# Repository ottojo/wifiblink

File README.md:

## Wiring
| Shield |  GPIO   | WEMOS |
|--------|:-------:|------:|
| Output | GPIO 14 |    D5 |
| LED 1  | GPIO 12 |    D6 |
| LED 2  | GPIO 13 |    D7 |
| Button | GPIO 15 |    D8 |

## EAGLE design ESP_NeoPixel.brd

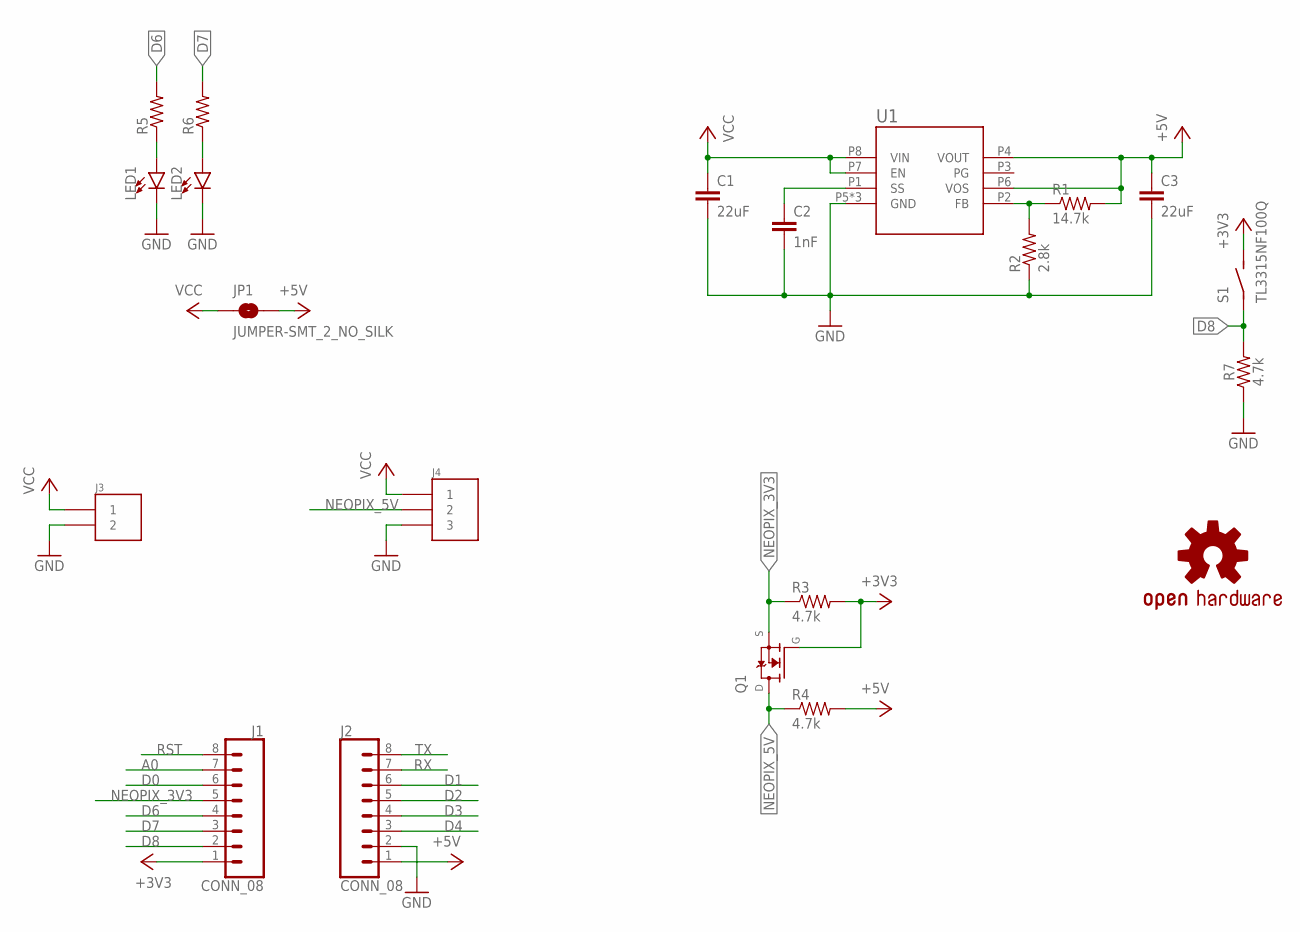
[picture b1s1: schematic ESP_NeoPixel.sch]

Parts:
C1, C3: 22uF; 0805
C2: 1nF; 0603
J1, J2: CONN_08; 1X08_LOCK_NO_SILK
J3: MKDS3-2-5.00
J4: MKDS3-3-5.00
JP1: JUMPER-SMT_2_NO_SILK; SMT-JUMPER_2_NO_SILK
LED1, LED2: LED0603; LED-0603
LOGO1: OSHW-LOGOS; OSHW-LOGO-S
Q1: BSN20,215; BSN20_215
R1: 14.7k; 0603
R2: 2.8k; 0603
R3, R4, R7: 4.7k; 0603
R5, R6: 0603
S1: TL3315NF100Q
U1: LMZ21700; SIL0008E

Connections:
+3V3: J1.1, Q1.1 (G), R3.2, S1.P3 (S), S1.P4 (S)
+5V: C3.1, J2.1, JP1.2, R1.2, R4.2, U1.P4 (VOUT), U1.P6 (VOS)
A0: J1.7
D0: J1.6
D1: J2.6
D2: J2.5
D3: J2.4
D4: J2.3
D6: J1.4, R5.2
D7: J1.3, R6.2
D8: J1.2, R7.2, S1.P1, S1.P2
GND: C1.2, C2.2, C3.2, J2.2, J3.2, J4.3, LED1.C, LED2.C, R2.1, R7.1, U1.P5 (GND), U1.P9 (GND), U1.P10 (GND)
unnamed: R1.1, R2.2, U1.P2 (FB)
unnamed: C2.1, U1.P1 (SS)
unnamed: LED1.A, R5.1
unnamed: LED2.A, R6.1
NEOPIX_3V3: J1.5, Q1.2 (S), R3.1
NEOPIX_5V: J4.2, Q1.3 (D), R4.1
RST: J1.8
RX: J2.7
TX: J2.8
VCC: C1.1, J3.1, J4.1, JP1.1, U1.P7 (EN), U1.P8 (VIN)

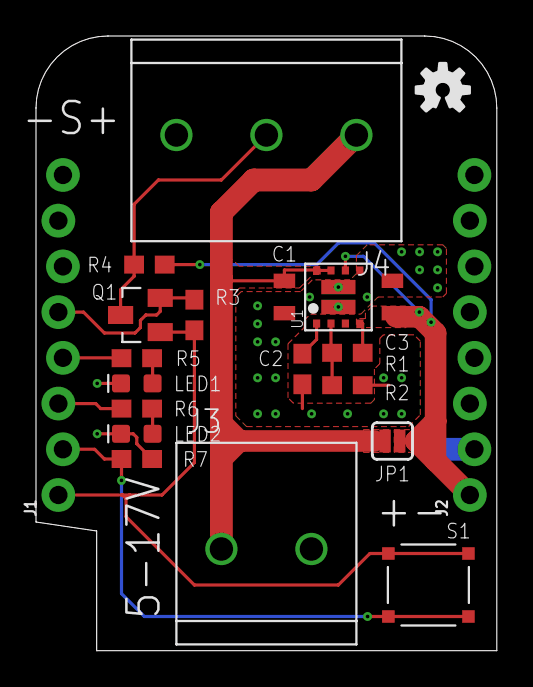
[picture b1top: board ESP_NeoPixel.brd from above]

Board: 2 copper layers, 25.6 x 34.1 mm, 21 parts (0 on the bottom side), 13 nets.

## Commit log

2018-09-29 dimensions and wemos pins
2018-09-30 did the thing
2018-09-30 values, silkscreen
2018-09-30 silkscreen, gnd connection to esp
2018-09-30 leds
2018-09-30 various layout changes
    used sparkfun libraries
2018-09-30 silkscreen fixes
2018-09-30 via stop limit, U1 pin1 marker
2018-09-30 added switch to D8
2018-09-30 silkscreen alignment
2022-12-03 Added wiring information

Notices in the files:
parts and their libraries:
SparkFun-Jumpers: Licensing: Creative Commons ShareAlike 4.0 International - https://creativecommons.org/licenses/by-sa/4.0
